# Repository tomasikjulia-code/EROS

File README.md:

# Rythmio

**Low-Cost ECG Holter**

## System Overview
Rythmio is an integrated, low-cost ambulatory electrocardiogram (ECG) monitoring system designed for continuous cardiac acquisition. The project encompasses a custom-designed hardware front-end, an embedded microcontroller executing a Real-Time Operating System (RTOS), a mobile application for data telemetry and visualization, and mechanical CAD designs for the device housing.

## Repository Structure

* **`3D Models/`**: Mechanical CAD files defining the physical enclosure.
* **`Embedded Software/`**: Firmware implemented in C and C++ operating within an RTOS framework. This directory includes hardware abstraction layers, deterministic task scheduling, and peripheral drivers.
* **`Media/`**: Visual documentation and media assets detailing the prototype iterations.
* **`MobileApp/`**: React Native based mobile application source code responsible for device configuration, state monitoring, and telemetry data parsing.
* **`PCB/`**: Schematic diagrams, printed circuit board layouts, and documentation of the boards.
* **`Prototype/`**: Complete implementation of initial hardware and software version.
* **`Software/PCB_Software/`**: Auxiliary software utilities designed for debugging, test automation, and preliminary board bring-up.

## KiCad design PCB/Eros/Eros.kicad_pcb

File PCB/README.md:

## Piny ESP32:
 - GPIO0: do boot; najlepiej podciągnąć do 3.3V przez rezystor 10Kom i dodać przycisk, który ściąga do GND;
 - GPIO2: podczas wchodzenia w tryb programowania, pin musi być w stanie niskim lub niepodłączonym; póżniej już nie ma znaczenia jaki ma stan;
  - GPIO5: ma wewnętrzny pull-up, nie ma znaczenia, gdy gpio0 i gpio2 są poprawnie ustawione, unikać urządzeń które przy starcie wymuszają stan niski;
 - GPIO6-GPIO11 są do pamięci flash;
 - GPIO12:jeśli trzeba użyć jako gpio(bo wszystkie inne zajęte) to trzeba się upewnić, że przy starcie nie wymuszany jest stan wysoki;
 - GPIO15: ma wewnątrz pull-up więc domyślnie jest na 3.3V, można używać jako GPIO; on odpowiada za to, że w trminalu jest boot:0x13 (SPI_FAST_FLASH_BOOT),
gdy przy włączaniu esp32, będzie na stan 0 to esp32 będzie milczeć podczas startu, na schemacie w dokumentacji nie widać rezystora podciągającego, 
co oznacza że wewnątrz krzemu jest podciągnięcie i one jest bardzo słabe. jak się chce być w 100% pewnym to można podciągnąć go zewnętrznie do 3.3V;
 - Na pin VDD można podpiąć napięcie od 3.0V do 3.6V.

## PINY DO PERYFERIÓW:
 - CZYTNIK KARTY SD: VSPI_MISO -> GPIO19, VSPI_MOSI -> GPIO23, SS/CS -> GPIO32, VSPI_SCK -> GPIO18;
 - MODUŁ EKG: START -> GPIO25, PWDN -> GPIO26, HSPI_CS -> GPIO15, HSPI_MOSI -> GPIO13, HSPI_SCK -> GPIO12, HSPI_MISO -> GPIO14;
 - WYŚWIETLACZ: Busy_pin -> GPIO4, CS_pin -> GPIO5, DC_Pin -> GPIO17, RST_Pin -> GPIO16, VSPI_SCK_Pin -> GPIO18 , VSPI_MOSI_pin -> GPIO23;
 - PRZYCISKI: piny: BUTTON1 -> GPIO35, BUTTON2 -> GPIO39;
 - AKCELEROMETR: I2C: SDA -> GPIO21 i SCL -> GPIO22;
 - BUZZER -> GPIO27
 - SEKCJA POWER: ADC -> GPIO36

## Schemat PCB

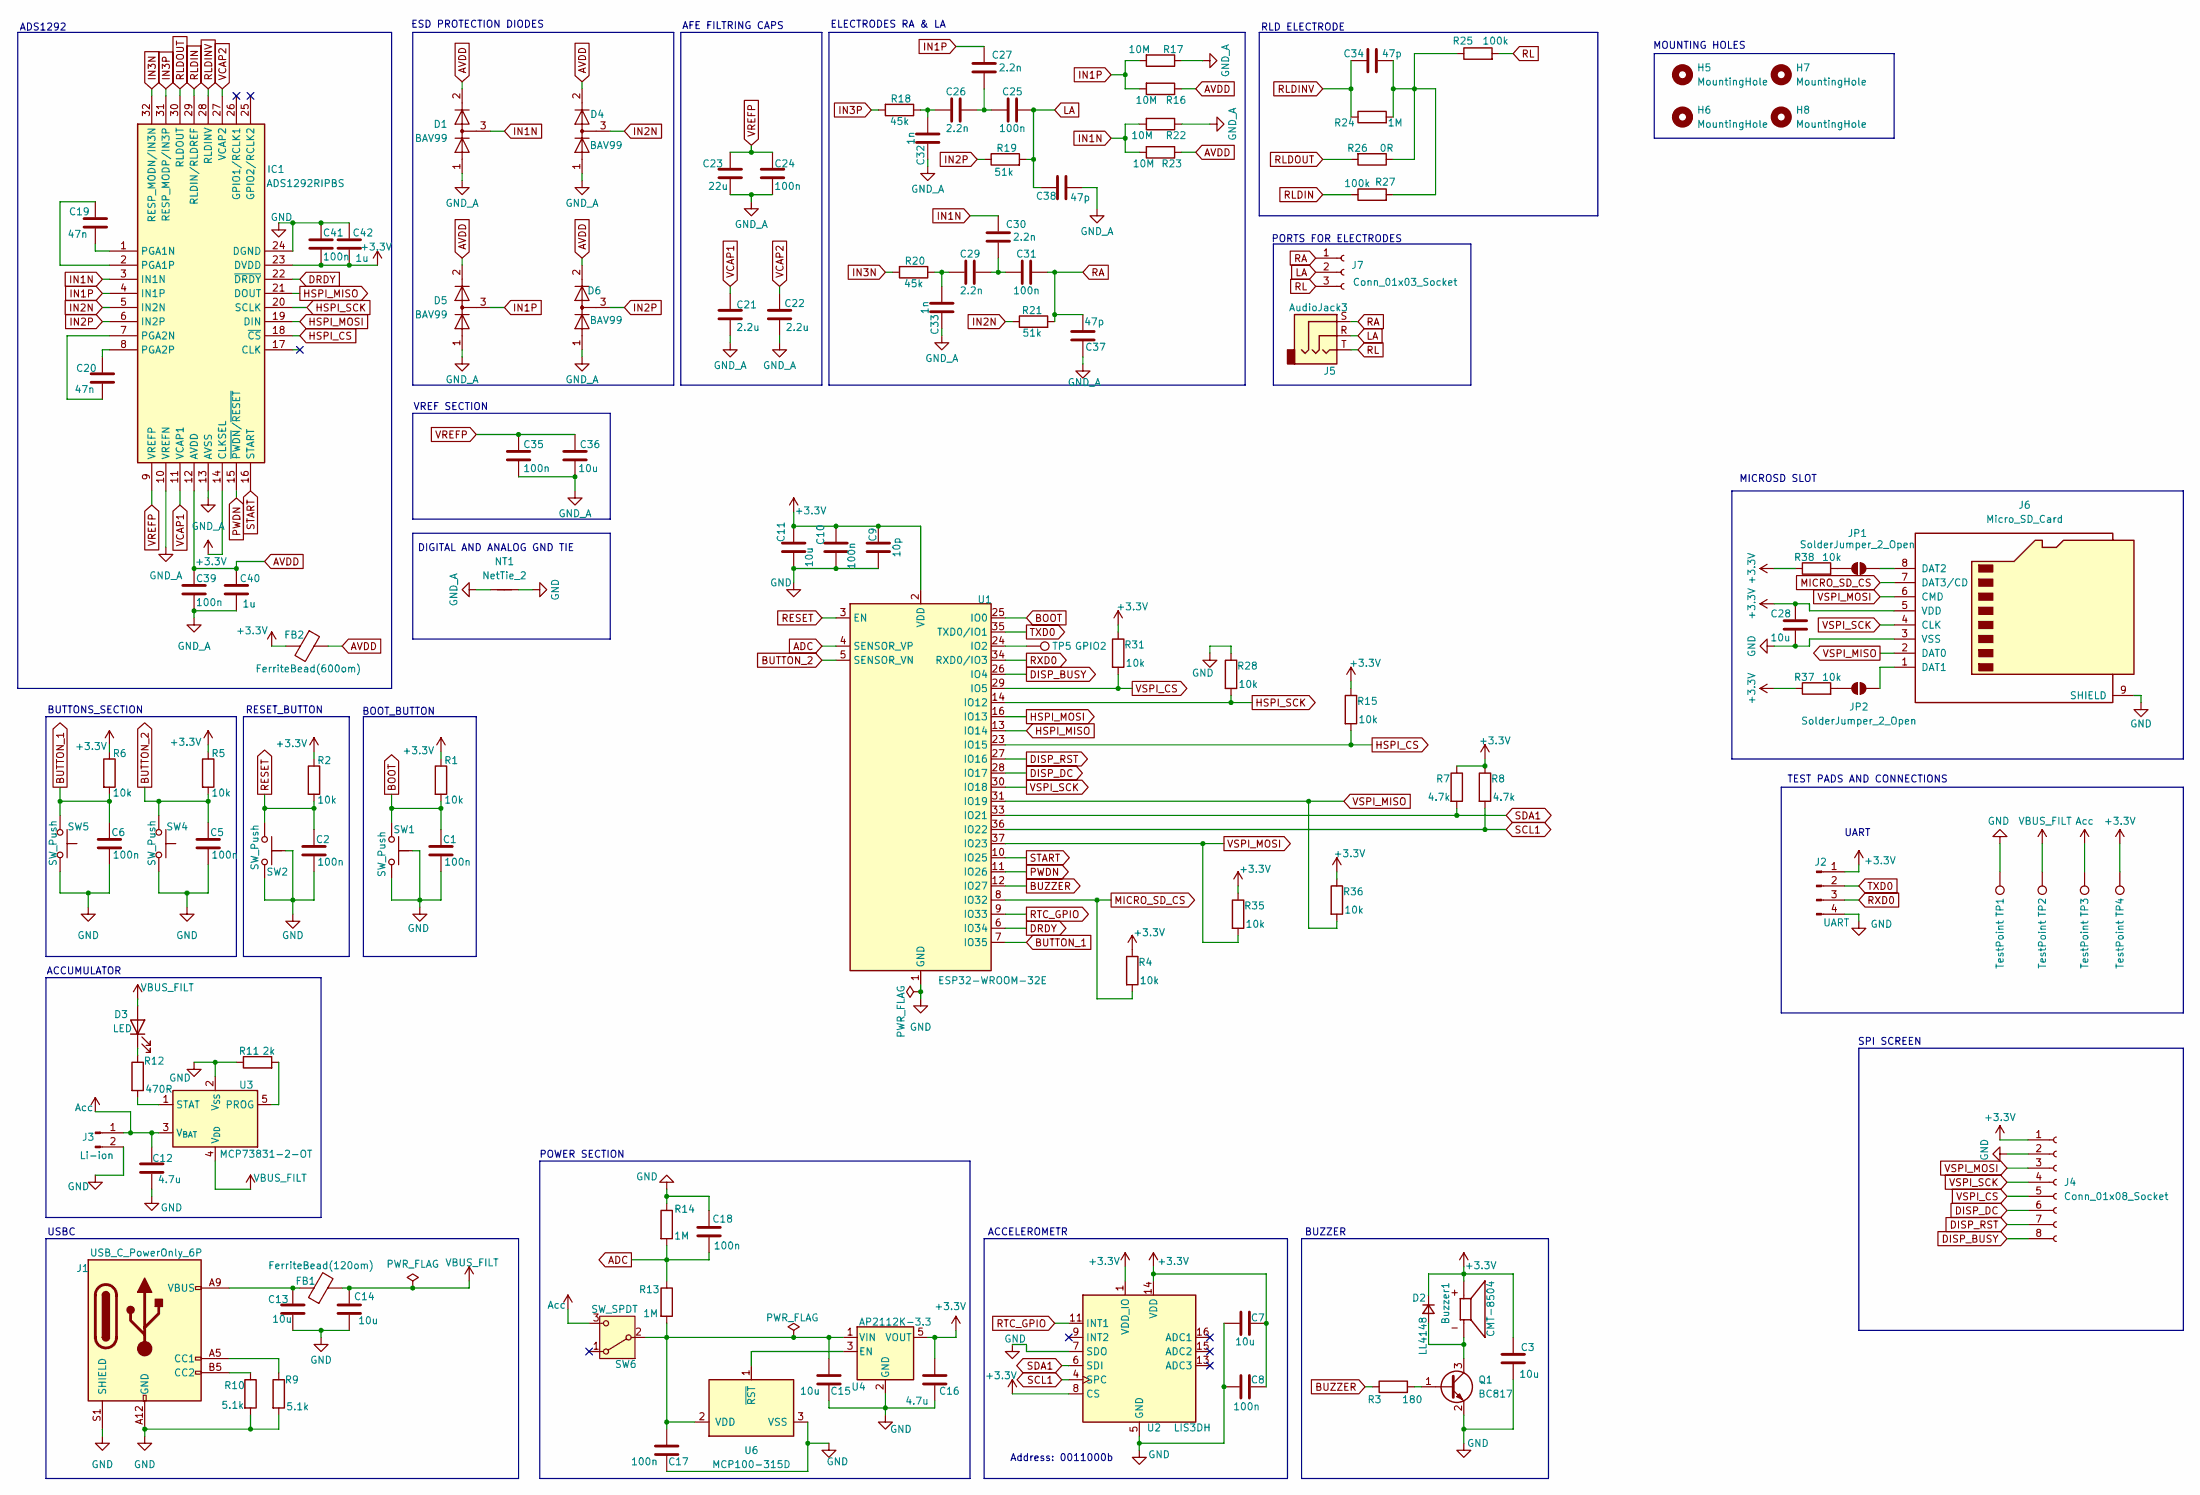
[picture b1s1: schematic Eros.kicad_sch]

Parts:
Buzzer1: CMT-8504; XDCR_CMT-8504-100-SMT-TR; PARTREV 1.0
C1, C2, C5, C6, C8, C10, C17, C18, C24, C25, C31, C35, C39, C41: 100n; C_0402_1005Metric_Pad0.74x0.62mm_HandSolder
C3, C7, C11, C13, C14, C15, C28, C36: 10u; C_0603_1608Metric_Pad1.08x0.95mm_HandSolder
C9: 10p; C_0402_1005Metric_Pad0.74x0.62mm_HandSolder
C12, C16: 4.7u; C_0603_1608Metric_Pad1.08x0.95mm_HandSolder
C19, C20: 47n; C_0402_1005Metric_Pad0.74x0.62mm_HandSolder
C21, C22: 2.2u; C_0402_1005Metric_Pad0.74x0.62mm_HandSolder
C23: 22u; C_0402_1005Metric_Pad0.74x0.62mm_HandSolder
C26, C27, C29, C30: 2.2n; C_0402_1005Metric_Pad0.74x0.62mm_HandSolder
C32, C33: 1n; C_0402_1005Metric_Pad0.74x0.62mm_HandSolder
C34, C37, C38: 47p; C_0402_1005Metric_Pad0.74x0.62mm_HandSolder
C40, C42: 1u; C_0402_1005Metric_Pad0.74x0.62mm_HandSolder
D1, D4, D5, D6: BAV99; SOT-23
D2: LL4148; D_MiniMELF_Handsoldering
D3: LED; LED_0402_1005Metric_Pad0.77x0.64mm_HandSolder
FB1: FerriteBead(120om); L_0402_1005Metric_Pad0.77x0.64mm_HandSolder
FB2: FerriteBead(600om); L_0402_1005Metric_Pad0.77x0.64mm_HandSolder
H5, H6, H7, H8: MountingHole; MountingHole_3.2mm_M3_Pad
IC1: ADS1292RIPBS; QFP50P700X700X120-32N; Mouser Part Number 595-ADS1292RIPBS
J1: USB_C_PowerOnly_6P; USB_C_Receptacle_GCT_USB4125-xx-x_6P_TopMnt_Horizontal
J2: UART; PinHeader_1x04_P2.54mm_Vertical
J3: Li-ion; JST_PH_B2B-PH-K_1x02_P2.00mm_Vertical
J4: Conn_01x08_Socket; JST_PH_B8B-PH-K_1x08_P2.00mm_Vertical
J5: AudioJack3; Jack_3.5mm_Lumberg_1503_03_Horizontal
J6: Micro_SD_Card; microSD_HC_Molex_47219-2001
J7: Conn_01x03_Socket; PinHeader_1x03_P2.54mm_Vertical
JP1, JP2: SolderJumper_2_Open; SolderJumper-2_P1.3mm_Open_Pad1.0x1.5mm
NT1: NetTie_2; NetTie-2_SMD_Pad0.5mm
Q1: BC817; SOT-23
R1, R2, R4, R5, R6, R15, R28, R31, R35, R36, R37, R38: 10k; R_0402_1005Metric_Pad0.72x0.64mm_HandSolder
R3: 180; R_0402_1005Metric_Pad0.72x0.64mm_HandSolder
R7, R8: 4.7k; R_0402_1005Metric_Pad0.72x0.64mm_HandSolder
R9, R10: 5.1k; R_0402_1005Metric_Pad0.72x0.64mm_HandSolder
R11: 2k; R_0402_1005Metric_Pad0.72x0.64mm_HandSolder
R12: 470R; R_0402_1005Metric_Pad0.72x0.64mm_HandSolder
R13, R14, R24: 1M; R_0402_1005Metric_Pad0.72x0.64mm_HandSolder
R16, R17, R22, R23: 10M; R_0402_1005Metric_Pad0.72x0.64mm_HandSolder
R18, R20: 45k; R_0402_1005Metric_Pad0.72x0.64mm_HandSolder
R19, R21: 51k; R_0402_1005Metric_Pad0.72x0.64mm_HandSolder
R25, R27: 100k; R_0402_1005Metric_Pad0.72x0.64mm_HandSolder
R26: 0R; R_0402_1005Metric_Pad0.72x0.64mm_HandSolder
SW1, SW2: SW_Push; SW_Push_1P1T-SH_NO_CK_KMR2xxG
SW4, SW5: SW_Push; SW_Tactile_SPST_Angled_PTS645Vx39-2LFS
SW6: SW_SPDT; SW_SPDT_PCM12
TP1, TP2, TP3, TP4: TestPoint; TestPoint_Pad_D1.5mm
TP5: GPIO2; TestPoint_Pad_D1.5mm
U1: ESP32-WROOM-32E
U2: LIS3DH; LGA-16_3x3mm_P0.5mm_LayoutBorder3x5y
U3: MCP73831-2-OT; SOT-23-5
U4: AP2112K-3.3; SOT-23-5
U6: MCP100-315D; SOT-23

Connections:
+3.3V: Buzzer1.P, C3.1, C7.2, C8.2, C9.2, C10.2, C11.2, C16.2, C28.1, C41.2, C42.2, D2.1 (K), FB2.2, IC1.14 (CLKSEL), IC1.23 (DVDD), J2.1, J4.1, J6.5 (VDD), R1.1, R2.1, R4.1, R5.1, R6.1, R7.1, R8.1, R15.1, R31.1, R35.1, R36.1, R37.1, R38.1, TP4.1, U1.2 (VDD), U2.1 (VDD_IO), U2.8 (CS), U2.14 (VDD), U4.5 (VOUT)
ADC: C18.2, R13.1, R14.2, U1.4 (SENSOR_VP)
AVDD: C39.1, C40.1, D1.2 (A), D4.2 (A), D5.2 (A), D6.2 (A), FB2.1, IC1.12 (AVDD), R16.1, R23.1
Acc: C12.1, J3.1, SW6.3 (C), TP3.1, U3.3 (V_{BAT})
BOOT: C1.1, R1.2, SW1.1, U1.25 (IO0)
BUTTON_1: C6.1, R6.2, SW5.1, U1.7 (IO35)
BUTTON_2: C5.1, R5.2, SW4.1, U1.5 (SENSOR_VN)
BUZZER: R3.1, U1.12 (IO27)
DISP_BUSY: J4.8, U1.26 (IO4)
DISP_DC: J4.6, U1.28 (IO17)
DISP_RST: J4.7, U1.27 (IO16)
DRDY: IC1.22 (~DRDY), U1.6 (IO34)
GND: C1.2, C2.2, C3.2, C5.2, C6.2, C7.1, C8.1, C9.1, C10.1, C11.1, C12.2, C13.2, C14.2, C15.1, C16.1, C17.1, C18.1, C28.2, C41.1, C42.1, IC1.24 (DGND), J1.A12 (GND), J1.B12 (GND), J1.S1 (SHIELD), J2.4, J3.2, J4.2, J6.3 (VSS), J6.9 (SHIELD), NT1.2, Q1.2 (E), R9.2, R10.2, R11.1, R14.1, R28.1, SW1.2, SW1.SH, SW2.1, SW2.SH, SW4.2, SW5.2, TP1.1, U1.1 (GND), U1.15 (GND), U1.38 (GND), U1.39 (GND), U2.5 (GND), U2.7 (SDO), U2.10 (GND), U2.12 (GND), U3.2 (V_{SS}), U4.2 (GND), U6.3 (VSS)
GND_A: C21.2, C22.2, C23.2, C24.2, C32.2, C33.2, C35.2, C36.2, C37.1, C38.2, C39.2, C40.2, D1.1 (K), D4.1 (K), D5.1 (K), D6.1 (K), IC1.10 (VREFN), IC1.13 (AVSS), NT1.1, R17.1, R22.1
HSPI_CS: IC1.18 (~CS), R15.2, U1.23 (IO15)
HSPI_MISO: IC1.21 (DOUT), U1.13 (IO14)
HSPI_MOSI: IC1.19 (DIN), U1.16 (IO13)
HSPI_SCK: IC1.20 (SCLK), R28.2, U1.14 (IO12)
IN1N: C30.1, D1.3 (K), IC1.3 (IN1N), R22.2, R23.2
IN1P: C27.1, D5.3 (K), IC1.4 (IN1P), R16.2, R17.2
IN2N: D4.3 (K), IC1.5 (IN2N), R21.1
IN2P: D6.3 (K), IC1.6 (IN2P), R19.1
IN3N: IC1.32 (RESP_MODN/IN3N), R20.2
IN3P: IC1.31 (RESP_MODP/IN3P), R18.2
LA: C25.1, C38.1, J5.R, J7.2, R19.2
MICRO_SD_CS: J6.7 (DAT3/CD), R4.2, U1.8 (IO32)
unnamed: C13.1, FB1.1, J1.A9 (VBUS), J1.B9 (VBUS)
unnamed: C25.2, C26.1, C27.2
unnamed: C26.2, C32.1, R18.1
unnamed: C29.1, C30.2, C31.2
unnamed: C29.2, C33.1, R20.1
unnamed: C34.1, R24.2, R25.1, R26.1, R27.2
unnamed: Buzzer1.N, D2.2 (A), Q1.3 (C)
unnamed: D3.1 (K), R12.1
unnamed: C19.2, IC1.1 (PGA1N)
unnamed: C19.1, IC1.2 (PGA1P)
unnamed: C20.2, IC1.7 (PGA2N)
unnamed: C20.1, IC1.8 (PGA2P)
unnamed: J1.A5 (CC1), R9.1
unnamed: J1.B5 (CC2), R10.1
unnamed: J6.1 (DAT1), JP2.2 (B)
unnamed: J6.8 (DAT2), JP1.2 (B)
unnamed: JP1.1 (A), R38.2
unnamed: JP2.1 (A), R37.2
unnamed: Q1.1 (B), R3.2
unnamed: C15.2, C17.2, R13.2, SW6.2 (B), U4.1 (VIN), U6.2 (VDD)
unnamed: TP5.1, U1.24 (IO2)
unnamed: R11.2, U3.5 (PROG)
unnamed: R12.2, U3.1 (STAT)
unnamed: U4.3 (EN), U6.1 (~RST)
PWDN: IC1.15 (~PWDN/~RESET), U1.11 (IO26)
RA: C31.1, C37.2, J5.S, J7.1, R21.2
RESET: C2.1, R2.2, SW2.2, U1.3 (EN)
RL: J5.T, J7.3, R25.2
RLDIN: IC1.29 (RLDIN/RLDREF), R27.1
RLDINV: C34.2, IC1.28 (RLDINV), R24.1
RLDOUT: IC1.30 (RLDOUT), R26.2
RTC_GPIO: U1.9 (IO33), U2.11 (INT1)
RXD0: J2.3, U1.34 (RXD0/IO3)
SCL1: R8.2, U1.36 (IO22), U2.4 (SPC)
SDA1: R7.2, U1.33 (IO21), U2.6 (SDI)
START: IC1.16 (START), U1.10 (IO25)
TXD0: J2.2, U1.35 (TXD0/IO1)
VBUS_FILT: C14.1, D3.2 (A), FB1.2, TP2.1, U3.4 (V_{DD})
VCAP1: C21.1, IC1.11 (VCAP1)
VCAP2: C22.1, IC1.27 (VCAP2)
VREFP: C23.1, C24.1, C35.1, C36.1, IC1.9 (VREFP)
VSPI_CS: J4.5, R31.2, U1.29 (IO5)
VSPI_MISO: J6.2 (DAT0), R36.2, U1.31 (IO19)
VSPI_MOSI: J4.3, J6.6 (CMD), R35.2, U1.37 (IO23)
VSPI_SCK: J4.4, J6.4 (CLK), U1.30 (IO18)

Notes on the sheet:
ACCUMULATOR
DIGITAL AND ANALOG GND TIE
SPI SCREEN
AFE FILTRING CAPS
UART
POWER SECTION
Address: 0011000b
RESET_BUTTON
BUTTONS_SECTION
ACCELEROMETR
VREF SECTION
TEST PADS AND CONNECTIONS
BOOT_BUTTON
PORTS FOR ELECTRODES
MICROSD SLOT
USBC
ESD PROTECTION DIODES
ADS1292
BUZZER
RLD ELECTRODE
MOUNTING HOLES
ELECTRODES RA & LA

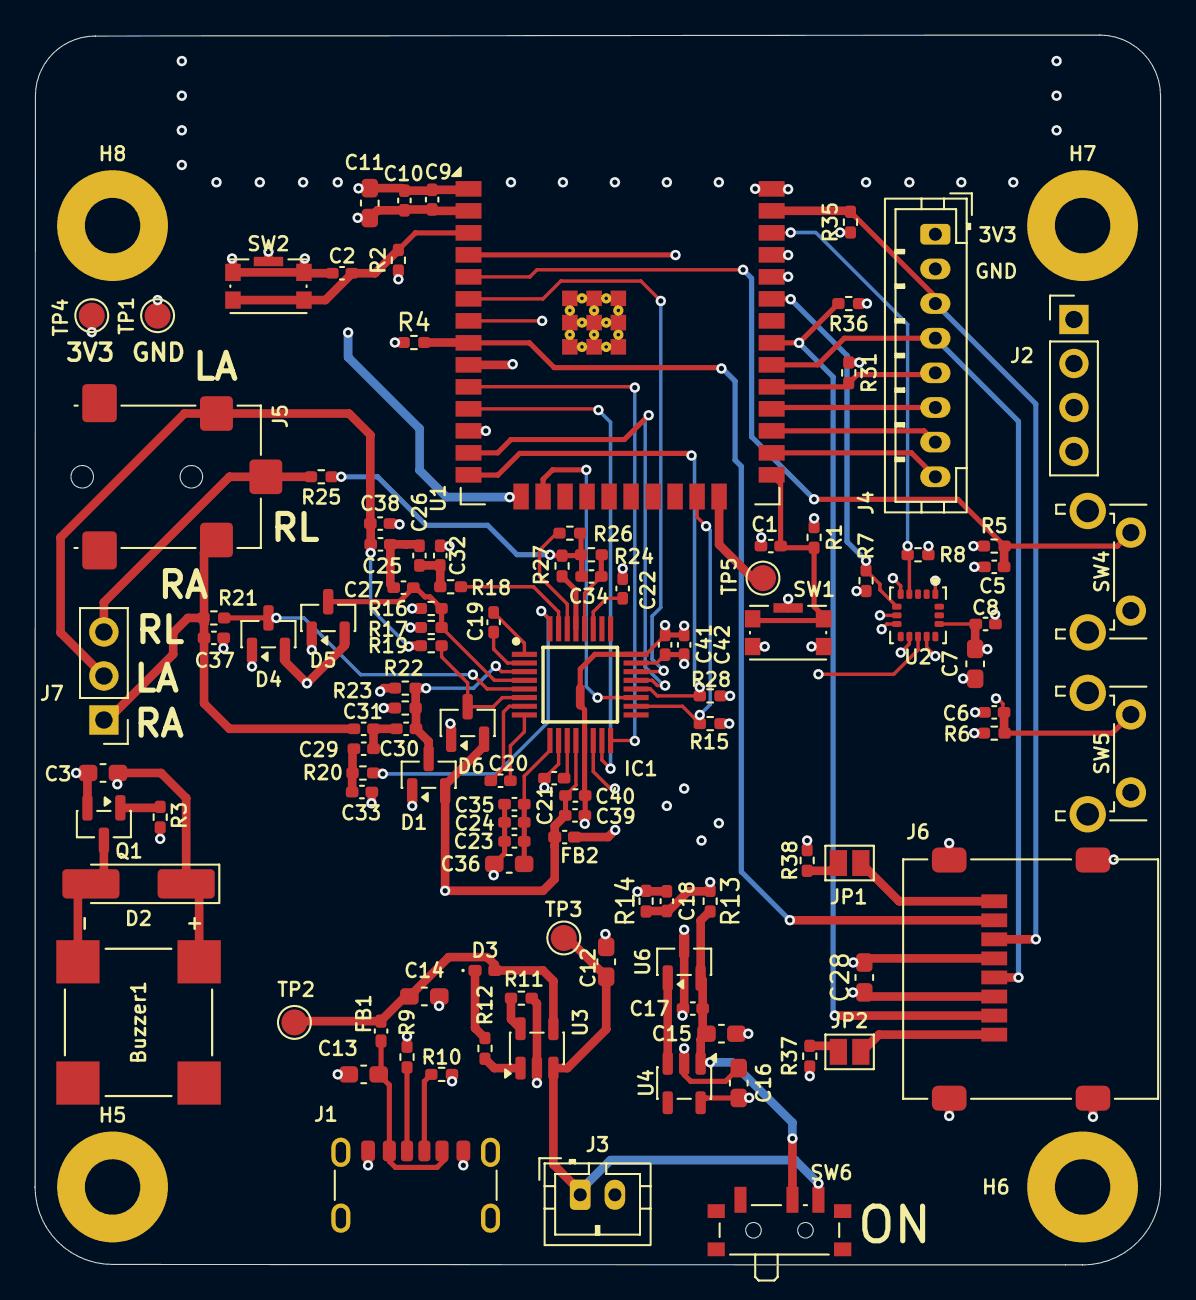
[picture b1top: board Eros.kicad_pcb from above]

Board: 4 copper layers, 65.0 x 71.0 mm, 115 parts (1 on the bottom side), 71 nets.

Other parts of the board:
G1: LOGO

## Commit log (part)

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2026-03-16 Pierwszy zapis projektu
2026-03-21 Funkcja modułu EKG
2026-03-21 Integrated EKG monitor with SD card wirting
2026-03-24 UI Prototype
2026-03-24 Removed PWR Pin
2026-03-24 Remove .vscode
2026-03-24 Dodanie folderu z projektem głównym opartym na freeRTOS. projekt łączy pozostałe komponenty za pomocą tasków
2026-03-26 Stworzenie projektu w KiCAD
2026-03-26 Dodanie Bootloadera
2026-03-27 usuniecie ds_store i utworzenie brancha
2026-03-27 Remove tracked .DS_Store files
2026-03-27 usuniecie ds.store
2026-03-27 dodanie manadzera urzadzenia ktory zarzadza peryferiami holtera
2026-03-27 usuniecie starych projektow
2026-03-28 dodanie taska Bluetooth
2026-03-29 Dodanie pierwszej wersji Frontend
2026-03-29 Dodanie opisu kompilacji
2026-03-29 rename PCB README
2026-03-29 Dodanie pliku .txt z informacjami do połączeń pcb
2026-03-29 Dodanie symbolu i footprintu buzzera w katalogu libs
2026-03-29 add microsd, spi, adc
2026-03-29 Dodanie sekcji zasilania oraz akcelerometru
2026-03-29 Dodanie sekcji buzzera i przycisków
2026-03-29 add .gitignore
2026-03-29 change project settings
2026-03-29 poprawa sekcji zasilania i dodanie power supply supervisor
2026-03-29 add AD8232 symbol
2026-03-29 add AD8232 footprint
2026-03-29 connect footprint to symbol
2026-03-29 connect ads
2026-03-30 Dodanie schematu modułu ad8232
2026-03-30 Add dnp filter resistors/capacitor
2026-03-30 wire ads1115
2026-03-30 ad TPs, align boxes
2026-03-31 change I2C labels
2026-03-31 Wire SDcard SPI
2026-03-31 add footprints and tps
2026-03-31 add VSPI and HSPI flags
2026-04-01 Poprawinie footprintów oraz naprawienie błędów ERC
2026-04-06 add 18650 holder footprint, verify and change notes
2026-04-06 flip battery
2026-04-06 wire waveshare Waveshare 12955 e-ink
2026-04-06 connect LOD+/-, add pinHeader for RA LA RL
2026-04-06 Wire OPA333
2026-04-06 Poprawiono odświeżanie, dodano widok wyboru czasu trwania badania, dodano ostrzeżenia
2026-04-07 Dodano widok zakończenia badania
2026-04-07 Wstępne rozmieszczenie brzegowych elementów
2026-04-08 Wstępne ułożenie komponentów
2026-04-11 Dekompozycja aplikacji mobilnej
2026-04-11 Dodanie komunikacji przez I2C z adc oraz dodanie algorytmu Pan Tompkinsa
2026-04-11 dodanie nowych funkcjonalnosci Bluetooth (aktywacja BT przyciskiem, przesyl na zywo probek EKG, przesyl pliku na zadanie aaplikacji), dodanie licznika trwania badania oraz wyswietlanie czasu pozostal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
2026-04-12 Dodanie bufora kolowego, wykresu live w aplikacji i symulacji odbioru danych z urzadzenia
2026-04-12 WIP: Dodano funkcje do łączenia przez bluetooth, łączy ale crashuje przy odbiorze danych
2026-04-13 Łączenie z Bluetooth, odbieranie diagnostyk urządzenia, wykres live
2026-04-14 Dodano request GET_ECG, zmieniono format wiadomości z diagnostyką
2026-04-15 integracja urzadzenia z aplikacja mobilna
2026-04-16 Dodanie przycisków do trybu na żywo i do pobrania pliku
2026-04-17 Poprawa schematu oraz ulozenie komponentow
2026-04-18 Podrasowanie wykresu live
2026-04-18 Dodanie obslugi widzetow na podstawie pliku
2026-04-19 poprawa czytelności sekcji zasilania
2026-04-19 zmiana komentarzy na aktualne
2026-04-19 poprawa bloku "RLD ELECTRODE"
2026-04-19 dodanie stackup jlcpcb_4L_1.6mm_outer1oz_inner1oz_NOREQ
2026-04-19 podpięcie zasilania
2026-04-20 Revert "Dodanie aktualizacji widżetów na podstawie danych z pliku"
2026-04-20 Revert "Revert "Dodanie aktualizacji widżetów na podstawie danych z pliku""
2026-04-20 Dodano przesył pliku do aplikacji
2026-04-20 wszystko poza ads
2026-04-20 Usunięte nadmiarowe logi
2026-04-20 ads in1p
2026-04-21 dodanie przesylania pliku w paczkach po 512 bajtow, dodanie sprawdzania stanu baterii przez dzielnik napiecia oraz odlaczenia elektrod
2026-04-21 wire HSPI
2026-04-21 wire everything
2026-04-21 Change copper clearance to 0.15mm, edge clearance to 0.4mm, hole diameter to 0.2mm, hole clearances to 0.25mm
2026-04-22 Clear Comments, write README.md
2026-04-22 update vias
2026-04-22 adjust stackup
2026-04-22 add logos
2026-04-24 Sprawdzenie schematu i połączeń
2026-04-26 Remove sharp edges
2026-04-26 Add gnd pour around antenna
2026-04-26 Add A GND
2026-04-26 add nettie
2026-04-26 Add separate AGND
2026-04-27 Connect GND and GND_A according to datasheet
2026-04-27 Działający wysył pliku w paczkach, poprawiono wyświetlanie wartości liczbowych i komunikatów
2026-04-27 Odbiór pliku w paczkach
2026-04-28 Dodanie średniej aktywności oraz wciskania przycisku oznaczającego ważne momenty do karty SD
2026-04-28 Dodanie podwujnego buforowania i integracja z aplikacja
2026-04-29 dodanie zdjęć
2026-04-29 dodanie szybszego przeszukiwania pliku i poprawa wysyłania
2026-04-30 Dodanie wykresu trendu aktywnosci
2026-04-30 Sztywne skalowanie
2026-05-01 Add BuzzerManager
2026-05-02 Dodanie algorytmu oznaczajacego szumy
2026-05-02 Dodanie algorytmu wykrywającego nieprawidłowości i uwzględnienie go w generowaniu raportu
2026-05-02 Dodanie logo, ekranu ładowania i zmiana nazwy aplikacji
2026-05-02 Usuniecie napisu z logo
2026-05-02 Add media/ folder with logo
2026-05-07 Add comarch logo and eros.xcf
2026-05-07 Dodanie funkcjonalnego przycisku usuwania pliku badania oraz paska ładowania przy przesyle pliku
2026-05-07 Dodanie kolumny important bo wcielo
2026-05-07 Ulepszenie paska ładowania na procentowy
2026-05-07 Dodanie dopasowywania do ekranu telefonu + update ikonki asystenta
2026-05-08 Usunięto plik font24.c
2026-05-09 Poprawione oznaczenia pinów
2026-05-09 change ADS library name
2026-05-09 update Q1 with library, change R13/R14 from C to R, change R18/R20 to 45k, change c28 to 0603 size
2026-05-10 Flip SD card orientation
2026-05-11 rozdzielenie kodu prototypu od kodu do nowej płytki pcb
2026-05-11 Zmiana struktury: przeniesienie projektów do folderu Prototype
2026-05-13 Dodanie poprawionego kodu działającego na pcb
2026-05-16 Generowanie AI raportu PDF
2026-05-16 Revert LiveEcgChart.js changes
2026-05-16 Dodanie ważnych zdarzeń oznaczanych przez użytkownika do raportu
2026-05-16 Uwzględnienie możliwości dodawania komentarzy pod ważnymi zdarzeniami
2026-05-16 Uporządkowanie przycisków w widoku raportu
2026-05-16 Dodanie funkcjonalności po stronie aplikacji mobilnej do przycisku usuwającego badanie z karty SD
2026-05-16 Wykomentowanie symulacji
2026-05-19 Rozwiazanie konfliktow
2026-05-19 Rozwiazanie konfliktow v2
2026-05-20 Skopiowanie aplikacji do folderu głównego i poprawa skalowania wykresu live
2026-05-20 Dodanie pełnoekranowego i skalowalnego wykresu
2026-05-21 Uzupelnienie funkcjonalnosci ustawien i historii
2026-05-26 Zmiana nazwy na RYTHMIO
2026-05-26 Poprawa działania przycisków, dodanie obsługi buzzera w sytuacji gdy zostaną odpięte elektrody oraz zwiększenie częstotliowści pobierania średniej aktywności fizycznej
2026-05-26 Dodanie potrójnego pikania gdy badanie się zakończy
2026-05-26 Dodanie logo w powiadomieniu
2026-05-26 dodano szybki skok w celu przemieszczenia kursora w wysylaniu pliku. dodano rowniez mozliwosc usuwania badania z karty SD z aplikacji oraz usuwanie przy kazdym wlaczeniu urządzenia.
2026-05-30 Rename PCB/ to Rythmio
2026-05-30 rename Media/ to Rythmio
2026-05-30 Add example README.md
2026-05-30 change README to Rythmio
2026-05-30 Wysyłanie rozmiaru posiadanego pliku, dynamiczny pasek pobierania
2026-06-01 Generowanie raportów z mocka
2026-06-02 zmiana nazwy urzadzenia BT
2026-06-04 .gitignore w Embedded Software
2026-06-04 Dodanie zabezpieczenia przed żądaniem dopisania nowego pliku
2026-06-05 Poprawione usuwanie w aplikacji, zmiana wyboru czasu trwania
2026-06-07 Checkpoint
2026-06-08 Przesył pliku
2026-06-08 Dodanie wysłania S przy nieotwarciu pliku
2026-06-09 Usuwanie pliku po resecie aplikacji
2026-06-09 Stworzenie strony internetowej
2026-06-09 poprawienie strony pod telefon
2026-06-09 Dodanie wysyłania badania emailem
2026-06-09 Sprzatanie
2026-06-10 zmiana logiki zapisu na karte SD, odciążenie sterty i zmiana alokacji niektorych obiektow
2026-06-11 dodanie trybu jasnego i dwujęzyczności
2026-06-12 poprawiono przesył badania po zakończeniu
2026-06-13 poprawy strony 12.06
2026-06-13 test usunięcia .html
2026-06-13 usunięcie html, poprawa stylu i języka
2026-06-14 ELEKTRONIKI
2026-06-14 WEB2 gitignore
2026-06-14 WEB2 init
2026-06-14 WEB2 blender src
2026-06-14 WEB2 readme od augmenta
2026-06-15 APP aplikacja do stawienia lokalnie
2026-06-15 WEB2 .gitignore fix
2026-06-15 WEB2 poprawki skalowania
2026-06-15 WEB2 poprawki pod małe mobilki
2026-06-15 WEB2 poprawa trybu ciemnego
2026-06-15 WEB2 i18n augment 100%
2026-06-15 WEB2 usunięcie poświaty
2026-06-15 WEB2 pipeline
2026-06-15 WEB2 poprawki builda
2026-06-15 WEB2 poprawki pipeline
2026-06-15 WEB2 poprawki pipeline - darmowe runnery
2026-06-17 poprawki opisów, poprawka modelu 3D, zdjęć oraz dodanie opinii i zakłądki o nas
2026-06-17 male poprawki sekcji o nas i sekcji opinii
2026-06-18 Usunięty timeout
2026-06-18 WEB2 wycięcie snap scrolling
2026-06-18 WEB2 poprawki viewport bez snap scrollingu
2026-06-18 poprawki strony i dodanie wiekszej ilosci opinii
2026-06-18 poprawki stringów i spójności opinii, usunięcie podkreślenia pod nagłówkiem
2026-06-18 Skrypt przyjmujący requesty z aplikacji
2026-06-19 APP mocki pod działanie w webówce
2026-06-19 APP mocki filestore
2026-06-21 APP analizy ai z wyborem dostawców
2026-06-21 APP poprawki ux
2026-06-21 fix AccelTask
2026-06-21 APP poprawki transferu i wyświetlania danych
2026-06-22 APP poprawki pdf, poprawki perf
2026-06-22 APP poprawki mock, transferu
2026-06-22 APP poprawki transferu
2026-06-22 APP refaktoryzacja
2026-06-24 APP poprawki poprawności wyliczenia transferu
2026-06-24 APP poprawka mocku bt
2026-06-24 APP poprawa paska przesyłu, dosyłania nowej części
2026-06-24 Dodałam zmianę progu dynamiczną, wykorzystywaną do liczenia bpm. Dodałam piknięcie buzzera jak zatwierdza się czas trwania badania oraz badanie rozpoczyna się od 1h a nie od 0
2026-06-24 APP poprawki odswiezania bpm, blokowania przyciskow i skali wykresu
2026-06-24 Poprawa dosyłu pliku
2026-06-24 APP Dodanie odbierania BPM od ESP
2026-06-25 zmniejszenie zuzycia ramu
2026-06-25 Ujednolicenie szerokosci wykresow
2026-06-25 poprawki przesylania i optymalizacje
2026-06-25 odkomentowanie debuggowania
2026-06-27 Poprawka progow aktywnosci
2026-06-27 APP Snippets fix
2026-06-28 poprawki
2026-06-28 dodanie alternatywnej opcji zapisu badania na wiele plikow
2026-06-28 dodanie opinii i zdjęcia COMARCH
